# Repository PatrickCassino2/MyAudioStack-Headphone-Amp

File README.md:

# MyAudioStack-Headphone-Amp
The Omicron headphone amplifier recreated in KiCad, with some updates

Derivative of Omicron, designed by @rus2000 on electro.ru & @alexcp on diyaudio.com

Original Project:
https://www.diyaudio.com/community/threads/omicron-a-compact-headphone-amp-with-140db-distortion.387033/

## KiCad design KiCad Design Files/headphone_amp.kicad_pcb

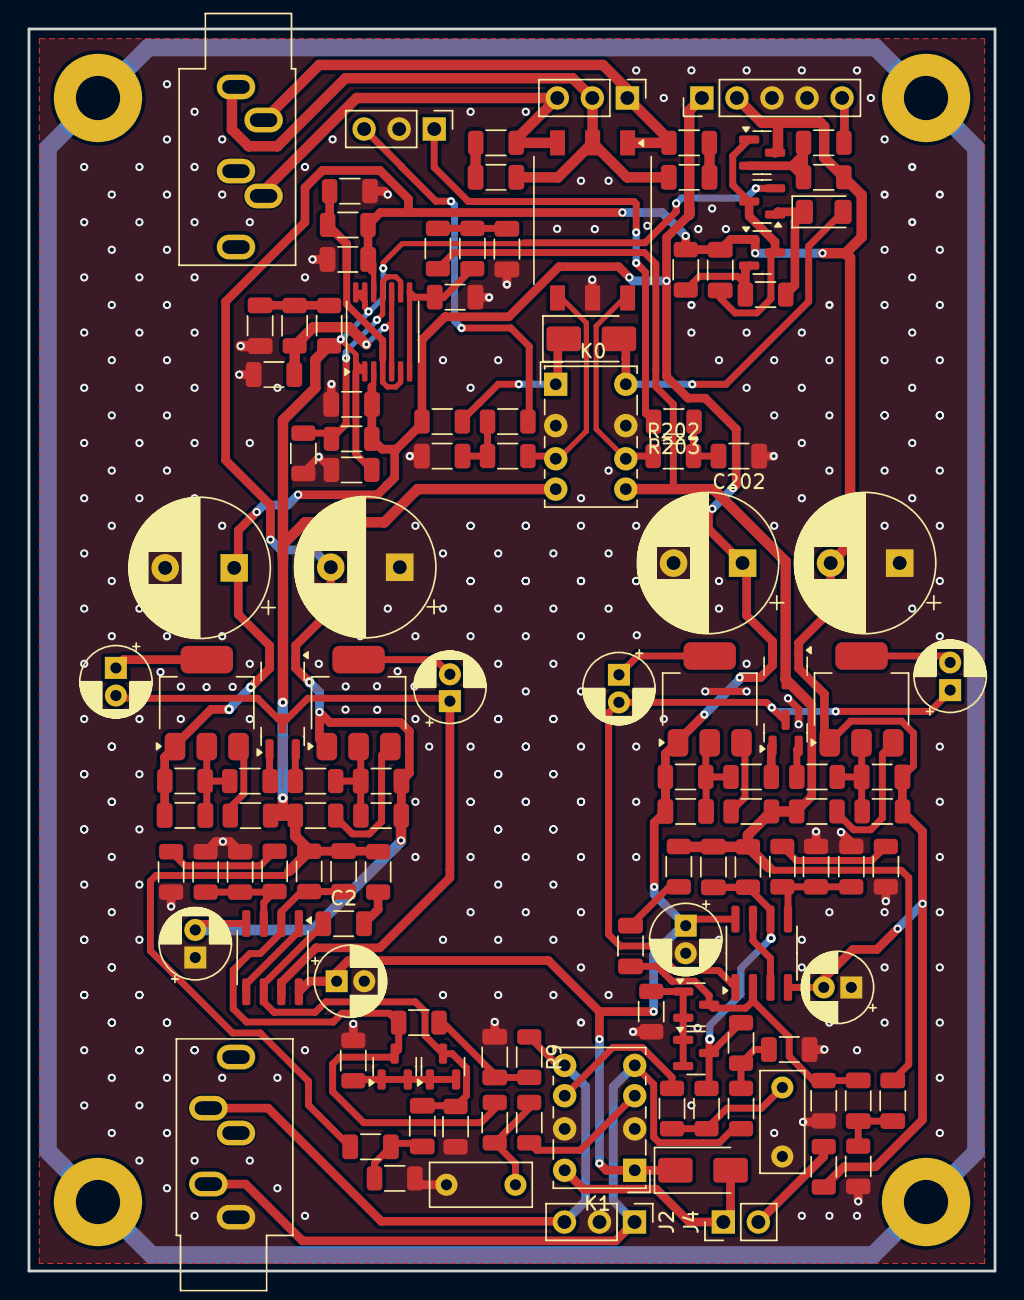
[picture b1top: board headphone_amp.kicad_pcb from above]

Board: 2 copper layers, 70.0 x 90.0 mm, 131 parts (0 on the bottom side), 71 nets.

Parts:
C0, C10: 5.6p; C_1206_3216Metric
C1, C101: 0.033u; C_Rect_L7.2mm_W3.0mm_P5.00mm_FKS2_FKP2_MKS2_MKP2
C2, C102: 0.01u; C_1206_3216Metric
C3, C9, C103, C109: 15p; C_1206_3216Metric
C4, C104, C202, C203: 330p; C_1206_3216Metric
C5, C105: 1500p; C_1206_3216Metric
C6, C8, C106, C108, C306, C307, C308, C309: 47u; CP_Radial_D5.0mm_P2.00mm
C7, C107: 680p; C_1206_3216Metric
C21, C22, C25, C26: 1000u; CP_Radial_D10.0mm_P5.00mm
C200, C201: 0.1u; C_1206_3216Metric
C204, C300, C301, C302, C303, C304, C305: 1u; C_1206_3216Metric
D5, D200: D; D_SMA
D100, D101, D102, D103, D104, D105, D106, D107: BAV99; SOT-23
D201: LED; D_1206_3216Metric
J2, J200, J202: Conn_01x03_Pin; PinHeader_1x03_P2.54mm_Vertical
J4: Conn_01x02_Pin; PinHeader_1x02_P2.54mm_Vertical
J203: Conn_01x05_Pin; PinHeader_1x05_P2.54mm_Vertical
K0, K1: G6K-2P-Y; Relay_DPDT_Omron_G6K-2P-Y
MH300, MH301, MH302, MH303: M3; MountingHole_3.2mm_M3_Pad
Q0, Q100: NPN; SOT-223-3_TabPin2
Q1, Q101: PNP; SOT-223-3_TabPin2
Q200, Q201: NMOS; SOT-23
Q202: PNP; SOT-23
R0, R1, R100, R101: 12k; R_1206_3216Metric
R2, R14, R102, R114: 15k; R_1206_3216Metric
R3, R103: 470k; R_1206_3216Metric
R4, R18, R104, R118: 10k; R_1206_3216Metric
R5, R105: 1k; R_1206_3216Metric
R6, R17, R106, R117, R200, R201, R202, R203, R204, R205, R306, R307: 100; R_1206_3216Metric
R7, R107: 300; R_1206_3216Metric
R8, R12, R108, R112: 2.2; R_1206_3216Metric
R9, R13, R109, R113: 1.3k; R_1206_3216Metric
R10, R11, R110, R111: 4.7k; R_1206_3216Metric
R15, R115: 24k; R_1206_3216Metric
R16, R39, R116, R206, R207, R208, R209, R210: 2.2k; R_1206_3216Metric
R300, R301: 20k; R_1206_3216Metric
R302, R303, R304, R305: 51k; R_1206_3216Metric
R308: 1M; R_1206_3216Metric
T200: 78602/3MC; Transformer_Wuerth_750315371
U0, U100: TLV9362; SOIC-8_3.9x4.9mm_P1.27mm
U300: LM339; TSSOP-14_4.4x5mm_P0.65mm

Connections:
+15V: C3.2, C21.1, C22.1, C103.2, C300.1, C306.1, C307.1, D5.1 (K), D102.2 (A), D107.2 (A), J203.1, K1.1, Q0.1 (C), Q100.1 (C), R4.2, R104.2, R206.1, R300.2, U0.8 (V+), U100.8 (V+), U300.3 (V+)
-15V: C9.1, C25.2, C26.2, C109.1, C204.2, C301.2, C308.2, C309.2, D102.1 (K), D107.1 (K), J203.2, Q1.1 (C), Q101.1 (C), Q200.3 (S), Q202.1 (C), R18.1, R39.2, R118.1, R208.1, R210.1, R301.2, U0.4 (V-), U100.4 (V-), U300.12 (V-)
/L_CROSS: K1.6, R100.1
/L_CROSS_R: C101.1, R100.2, R101.1
/L_INPUT: J2.1, K1.4, R109.1
/L_INPUT_R: C107.2, R109.2, R110.1
/L_IN_MIN: C10.1, D104.3 (K), R101.2, R102.1, R110.2, U100.6 (-)
/L_IN_MIN_R: C102.2, C104.1, D105.3 (K), R116.2, U100.2 (-)
/L_IN_POS: R111.2, R114.2, R115.2, U100.5 (+)
/L_IN_POS_R: U100.3 (+), U100.7
/L_IN_POS_RES: R111.1, R113.2
/R_CROSS: K1.3, R0.1
/R_CROSS_R: C1.1, R0.2, R1.1
/R_INPUT: J2.3, K1.5, R9.1
/R_INPUT_R: C7.2, R9.2, R10.1
/R_IN_MIN: C0.1, D100.3 (K), R1.2, R2.1, R10.2, U0.2 (-)
/R_IN_MIN_R: C2.1, C4.1, D101.3 (K), R16.2, U0.6 (-)
/R_IN_POS: R11.2, R14.2, R15.2, U0.3 (+)
/R_IN_POS_R: U0.1, U0.5 (+)
/R_IN_POS_RES: R11.1, R13.2
/R_OUT_R: C6.2, C8.1, D103.3 (K), U0.7
COMP_OUT: Q201.2 (G), R308.2, U300.1, U300.2, U300.13, U300.14
Earth: MH300.1, MH301.1, MH302.1, MH303.1
GND: C1.2, C7.1, C21.2, C22.2, C25.1, C26.1, C101.2, C107.1, C202.1, C203.2, C300.2, C301.1, C302.2, C303.2, C304.2, C305.2, C306.2, C307.2, C308.1, C309.1, J2.2, J200.2, J203.3, J203.4, K0.2, K0.7, K1.2, K1.7, R5.1, R7.1, R13.1, R14.1, R15.1, R16.1, R105.1, R107.1, R113.1, R114.1, R115.1, R116.1, R306.1, R307.1, R308.1, T200.5
GROUND_OUT: C200.1, C201.1, J202.2, T200.2
L_OUT: C10.2, C105.2, D107.3 (K), K0.5, R102.2, R103.2, R108.1, R112.2, R302.2
L_OUTPUT: J202.1, R200.1, T200.1
unnamed: C2.2, R3.1
unnamed: C4.2, C5.1, R7.2
unnamed: C102.1, R103.1
unnamed: C104.2, C105.1, R107.2
unnamed: C106.2, C108.1, D106.3 (K), U100.1
unnamed: C200.2, R200.2
unnamed: C201.2, R201.1
unnamed: C202.2, R202.2, R203.1
unnamed: C203.1, R204.2, R205.1
unnamed: C302.1, R302.1, R303.2
unnamed: C304.1, R304.1, R305.2
unnamed: D5.2 (A), J4.1, K1.8
unnamed: D100.1 (K), D100.2 (A), D101.1 (K), D101.2 (A), R5.2
unnamed: D103.2 (A), R17.1
unnamed: D103.1 (K), R6.1
unnamed: D104.1 (K), D104.2 (A), D105.1 (K), D105.2 (A), R105.2
unnamed: D106.2 (A), R117.1
unnamed: D106.1 (K), R106.1
unnamed: D200.2 (A), D201.2 (A), K0.8
unnamed: D200.1 (K), K0.1, R206.2
unnamed: D201.1 (K), Q201.1 (D), R209.2
unnamed: J4.2, R39.1
unnamed: J200.1, R203.2
unnamed: J200.3, R205.2
unnamed: J203.5, R207.1
unnamed: K0.3, R204.1, T200.4
unnamed: K0.6, R202.1, T200.6
unnamed: C3.1, C6.1, Q0.2 (B), R4.1, R6.2
unnamed: Q0.3 (E), R8.2
unnamed: C8.2, C9.2, Q1.2 (B), R17.2, R18.2
unnamed: Q1.3 (E), R12.1
unnamed: C103.1, C106.1, Q100.2 (B), R104.1, R106.2
unnamed: Q100.3 (E), R108.2
unnamed: C108.2, C109.2, Q101.2 (B), R117.2, R118.2
unnamed: Q101.3 (E), R112.1
unnamed: C204.1, Q200.1 (D), Q201.3 (S), Q202.3 (E)
unnamed: Q200.2 (G), R207.2, R208.2
unnamed: Q202.2 (B), R209.1, R210.2
unnamed: C305.1, R305.1, U300.5 (+), U300.10 (-)
unnamed: R301.1, R307.2, U300.4 (-), U300.6 (-)
unnamed: C303.1, R303.1, U300.7 (+), U300.8 (-)
unnamed: R300.1, R306.2, U300.9 (+), U300.11 (+)
R_OUT: C0.2, C5.2, D102.3 (K), K0.4, R2.2, R3.2, R8.1, R12.2, R304.2
R_OUTPUT: J202.3, R201.2, T200.3

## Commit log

2025-01-27 Initial commit of design and mfg files
